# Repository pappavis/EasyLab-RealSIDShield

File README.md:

# EasyLab-retro-synth-Commodore-64
Commodore 64 SID emulasie met Arduino

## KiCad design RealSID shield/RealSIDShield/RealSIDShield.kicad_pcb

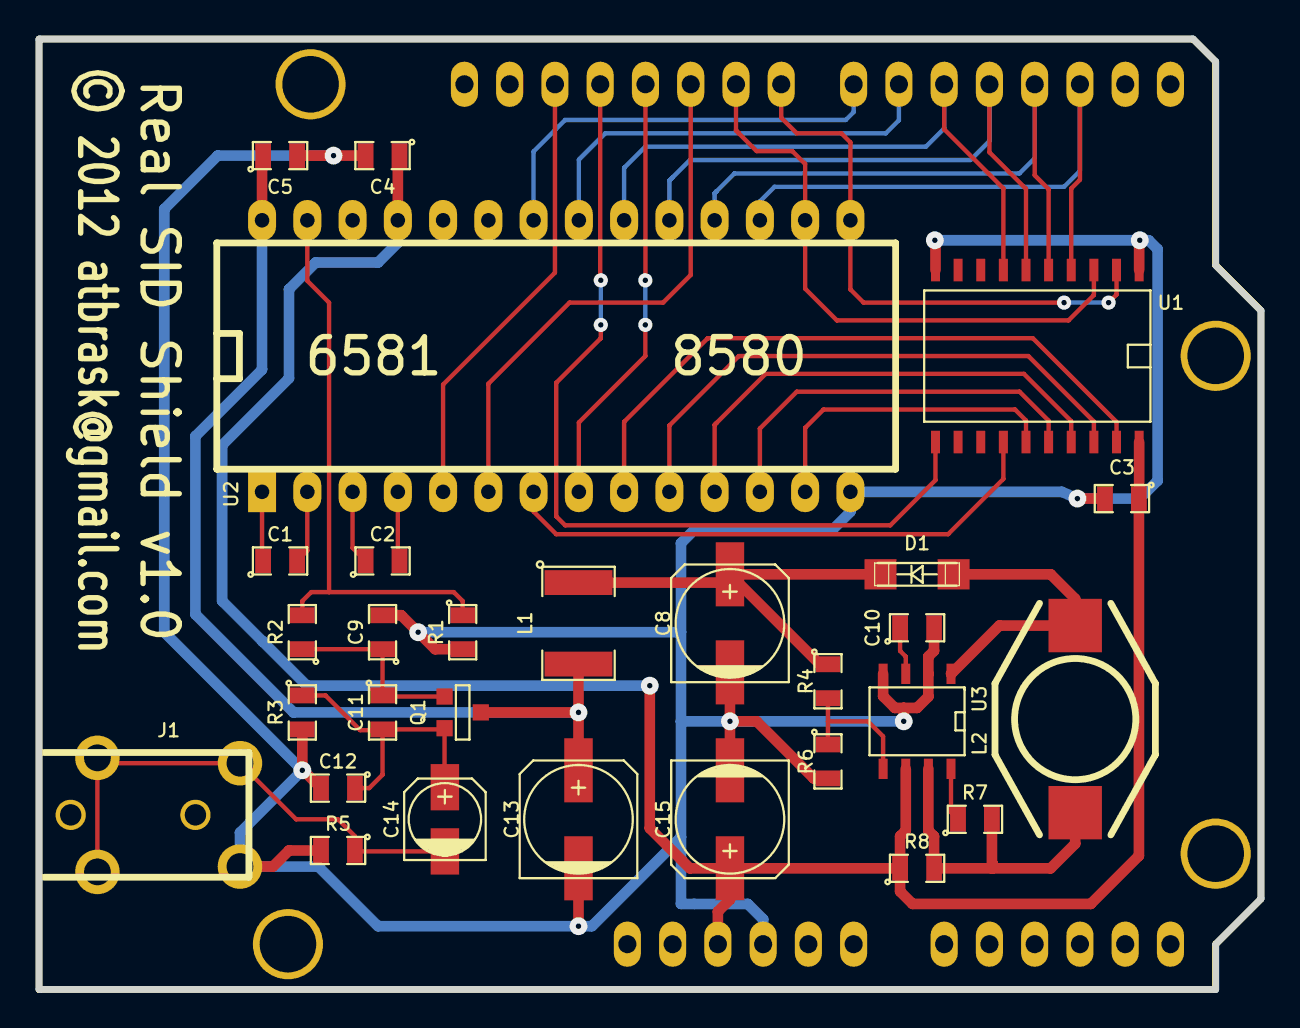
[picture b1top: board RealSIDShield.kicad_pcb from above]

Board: 2 copper layers, 68.6 x 53.3 mm, 30 parts (0 on the bottom side), 35 nets.

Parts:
C1, C2: 22nF_; SM0805
C3, C4, C5: 100nF; SM0805
C8, C13, C15: 100uF; c_elec_6.3x7.7
C9: 1nF; SM0805
C10: 560pF; SM0805
C11: 470pF; SM0805
C12: 220pF; SM0805
C14: 10uF; c_elec_4x5.3
D1: SK_34; diode-SMA-unfucked
J1: JACK_PLUG; MX-387GL
L1: 1uH; SM1812
L2: 330uH; Fastron_PISN
Q1: BC847; SOT23EBC
R1: NC_; SM0805
R2: 10K; SM0805
R3: 1K; SM0805
R4: 6k2_; SM0805
R5: 47K; SM0805
R6: 1k_; SM0805
R7: 180_ohm; SM0805
R8: 1.0_ohm; SM0805
SHIELD1: ARDUINO_SHIELD; ARDUINO_SHIELD_040pins
U1: 74574; SO20L
U2: SID CHIP; DIP-28__600_ELL
U3: MC34063; SO8E

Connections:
A0: U1.19, U2.9
A1: U1.18, U2.10
A2: U1.17, U2.11
A3: U1.16, U2.12
A4: U1.15, U2.13
D0: SHIELD1.8, U1.2, U2.15
D1: SHIELD1.9, U1.3, U2.16
D2: SHIELD1.2, U1.4, U2.17
D3: SHIELD1.3, U1.5, U2.18
D4: SHIELD1.4, U1.6, U2.19
D5: SHIELD1.5, U1.7, U2.20
D6: SHIELD1.6, U2.21
D7: SHIELD1.7, U2.22
GND: C3.2, C4.2, C5.2, C8.2, C9.2, C10.2, C12.2, C13.2, C15.2, J1.1, R1.2, R3.2, R5.2, R6.2, SHIELD1.GND1, U1.1, U1.10, U2.14, U3.2, U3.4
LATCH_CLOCK: SHIELD1.12, U1.11
unnamed: C1.2, U2.2
unnamed: R7.1, U3.8
unnamed: C10.1, U3.3
unnamed: C2.2, U2.4
unnamed: C2.1, U2.3
unnamed: C1.1, U2.1
unnamed: C11.2, C12.1, C14.1, Q1.1, R3.1
unnamed: C14.2, J1.2, J1.3, R5.1
unnamed: R1.1, R2.2, U2.27
unnamed: C9.1, C11.1, Q1.2, R2.1
unnamed: C8.1, D1.2, L1.1, R4.1
unnamed: R4.2, R6.1, U3.5
unnamed: D1.1, L2.1, U3.1
unnamed: L2.2, R7.2, R8.2, U3.7
R/W: U1.14, U2.7
SID_CLOCK: SHIELD1.10, U2.6
SID_CS: SHIELD1.11, U2.8
SID_RESET: SHIELD1.13, U2.5
VCC: C3.1, C4.1, C15.1, R8.1, SHIELD1.5V, U1.20, U2.25, U3.6
VDD: C5.1, C13.1, L1.2, Q1.3, U2.28

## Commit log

2018-04-05 :neckbeard: Added .gitattributes & .gitignore files
2018-04-05 eerste commit
2018-04-05 eerste commit 2
2018-11-12 ontwerp plaatjes toegevoegd

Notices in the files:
RealSID shield/RealSIDShield/RealSIDShield.kicad_pcb:
© 2012 atbrask@gmail.com
